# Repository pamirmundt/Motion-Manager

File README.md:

# Motion Manager (v1.0.0)
Controller for HNP Mikrosysteme micro annular gear pump MZR-7223
- 100 Hz PI RPM control with a RPM MAP filter
- 5 Hz screen refresh
- 31.250 Hz PWM frequency

## Future Improvements
- Spaghetti code
- SD card reader and LCD need different SPI busses. (because LCD SPI does not have a CS option where SPI messes)
- 24V converter for fixed input
- Converter efficiency and heat problems with linear regulators (Linear regulator must be replaced with a switching converter)
- Voltage protection
- SPI is not enough for LCD, additional data bus lines should be used for feedback from LCD

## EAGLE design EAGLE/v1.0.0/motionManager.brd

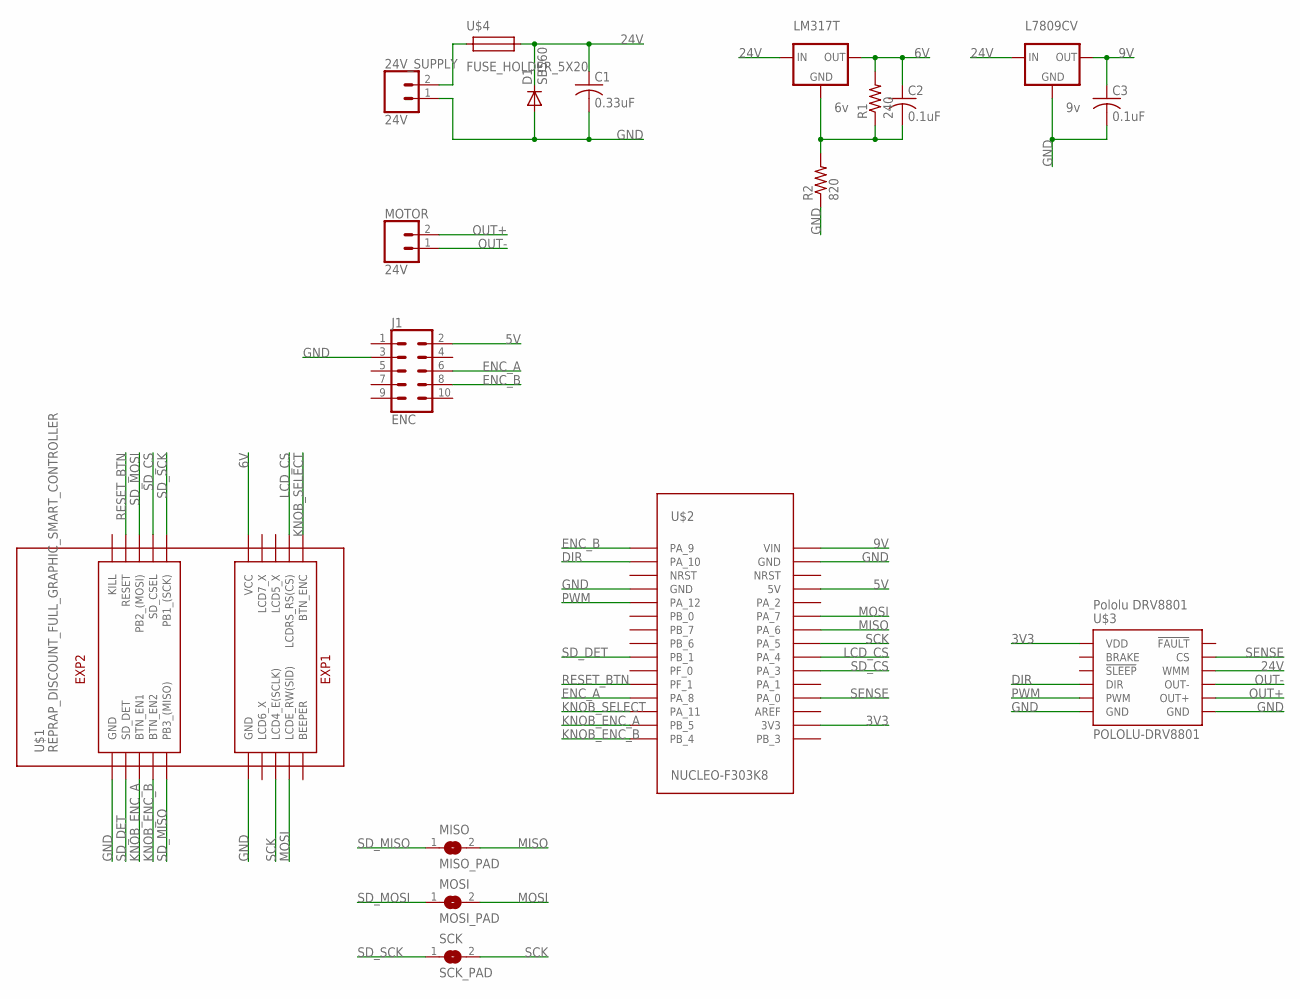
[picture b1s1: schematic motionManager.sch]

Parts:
24V_SUPPLY: 24V; SCREWTERMINAL-5MM-2
C1: 0.33uF; C025_050-055X075
C2, C3: 0.1uF; C025_050-055X075
D1: SB560; DO201-15
J1: ENC; 2X5-SHROUDED-NS
L7809CV: 9v; 78XXL
LM317T: 6v; 78XXL
MISO: MISO_PAD; SJW
MOSI: MOSI_PAD; SJW
MOTOR: 24V; SCREWTERMINAL-5MM-2
R1: 240; 0207/7
R2: 820; 0207/7
SCK: SCK_PAD; SJW
U$1: REPRAP_DISCOUNT_FULL_GRAPHIC_SMART_CONTROLLER
U$2: NUCLEO-F303K8
U$3: POLOLU-DRV8801
U$4: FUSE_HOLDER_5X20

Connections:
3V3: U$2.3V3, U$3.VDD
5V: J1.2, U$2.5V
6V: C2.1, LM317T.OUT, R1.2, U$1.VCC
9V: C3.1, L7809CV.OUT, U$2.VIN
24V: C1.1, D1.C, L7809CV.IN, LM317T.IN, U$3.VMM (WMM), U$4.P$2
DIR: U$2.PA_10, U$3.DIR
ENC_A: J1.6, U$2.PA_8
ENC_B: J1.8, U$2.PA_9
GND: 24V_SUPPLY.1, C1.2, C3.2, D1.A, J1.3, L7809CV.GND, R2.1, U$1.GND@0 (GND), U$1.GND@1 (GND), U$2.GND@0 (GND), U$2.GND@1 (GND), U$3.GND@1 (GND), U$3.GND@2 (GND)
KNOB_ENC_A: U$1.BTN_EN1, U$2.PB_5
KNOB_ENC_B: U$1.BTN_EN2, U$2.PB_4
KNOB_SELECT: U$1.BTN_ENC, U$2.PA_11
LCD_CS: U$1.LCDRS_RS(CS), U$2.PA_4
MISO: MISO.2, U$2.PA_6
MOSI: MOSI.2, U$1.LCDE_RW(SID), U$2.PA_7
unnamed: 24V_SUPPLY.2, U$4.P$1
unnamed: C2.2, LM317T.GND, R1.1, R2.2
OUT+: MOTOR.2, U$3.OUT+
OUT-: MOTOR.1, U$3.OUT-
PWM: U$2.PA_12, U$3.PWM
RESET_BTN: U$1.RESET, U$2.PF_1
SCK: SCK.2, U$1.LCD4_E(SCLK), U$2.PA_5
SD_CS: U$1.SD_CSEL, U$2.PA_3
SD_DET: U$1.SD_DET, U$2.PB_1
SD_MISO: MISO.1, U$1.PB3_(MISO)
SD_MOSI: MOSI.1, U$1.PB2_(MOSI)
SD_SCK: SCK.1, U$1.PB1_(SCK)
SENSE: U$2.PA_0, U$3.CS

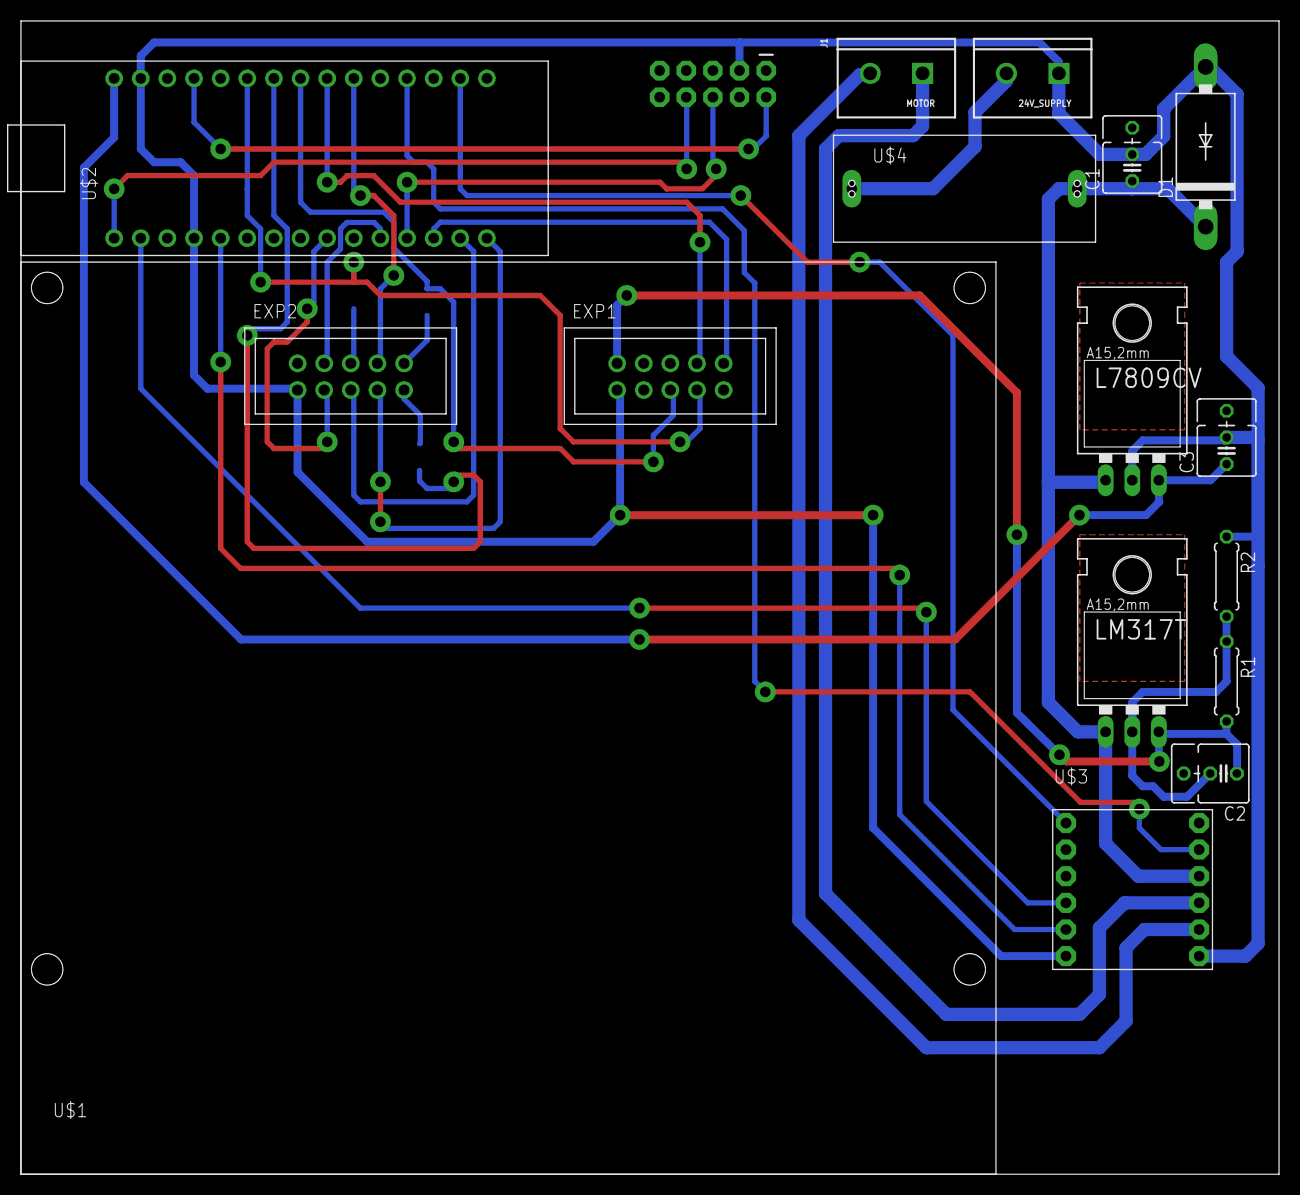
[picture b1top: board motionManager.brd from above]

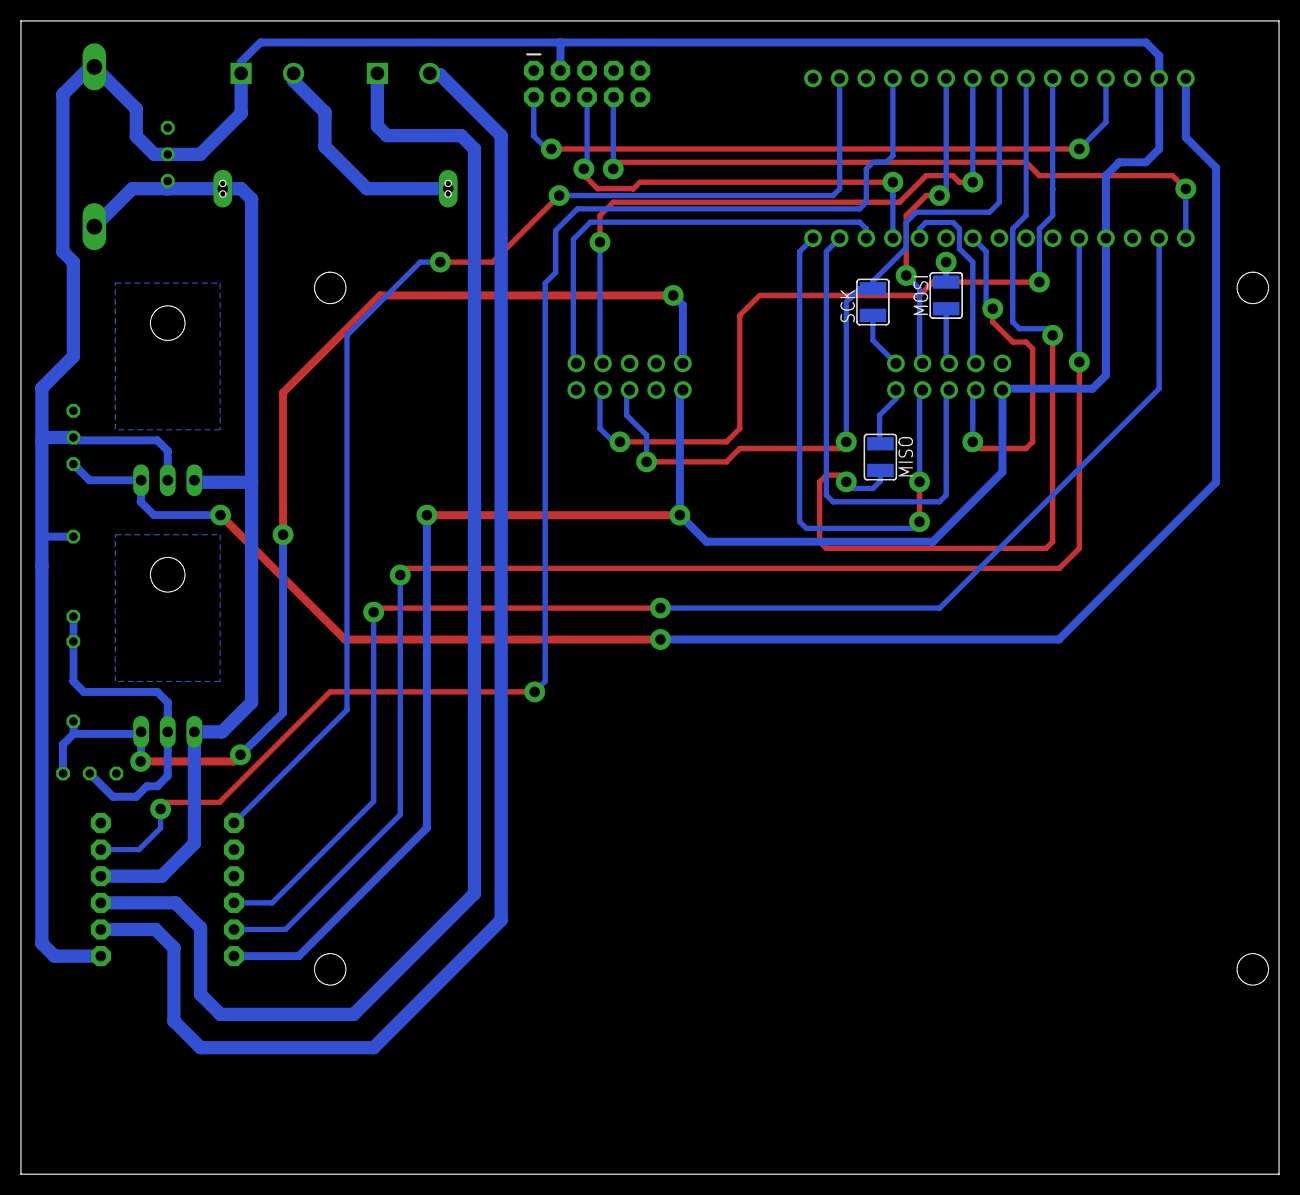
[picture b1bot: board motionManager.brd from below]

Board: 2 copper layers, 120.0 x 110.0 mm, 18 parts (3 on the bottom side), 28 nets.

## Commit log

2018-08-15 init

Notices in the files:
parts and their libraries:
SparkFun-Connectors: Licensing: Creative Commons ShareAlike 4.0 International - https://creativecommons.org/licenses/by-sa/4.0
